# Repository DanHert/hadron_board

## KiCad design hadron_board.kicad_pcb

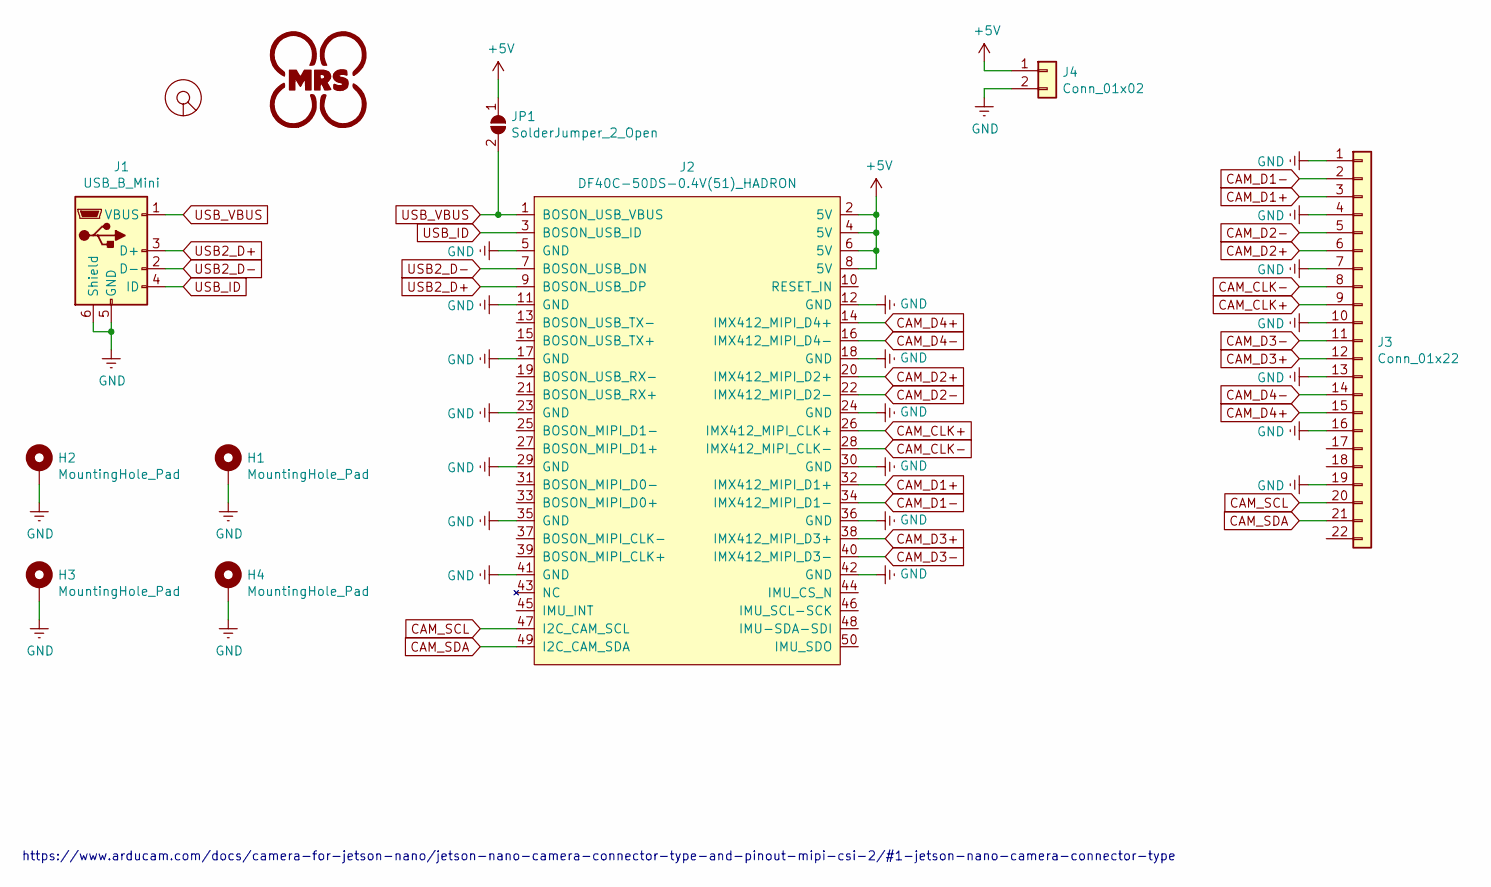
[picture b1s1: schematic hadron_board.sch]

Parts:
G1: LOGO; MRS_10mm
H1, H2, H3, H4: MountingHole_Pad; Mounting_hole_plated_1.7mm
J1: USB_B_Mini; USB_Mini-B_Lumberg_2486_01_Horizontal
J2: DF40C-50DS-0.4V(51)_HADRON; HRS_DF40C-50DS-0.4V(51)
J3: Conn_01x22; MOLEX_54548-2271
J4: Conn_01x02; Header_1x02_P2.54mm
JP1: SolderJumper_2_Open; SolderJumper-2_P1.3mm_Open_TrianglePad1.0x1.5mm
L1: logo; Logo_2mm

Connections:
+5V: J2.2 (5V), J2.4 (5V), J2.6 (5V), J2.8 (5V), J4.1, JP1.1 (A)
CAM_CLK+: J2.26 (IMX412_MIPI_CLK+), J3.9
CAM_CLK-: J2.28 (IMX412_MIPI_CLK-), J3.8
CAM_D1+: J2.32 (IMX412_MIPI_D1+), J3.3
CAM_D1-: J2.34 (IMX412_MIPI_D1-), J3.2
CAM_D2+: J2.20 (IMX412_MIPI_D2+), J3.6
CAM_D2-: J2.22 (IMX412_MIPI_D2-), J3.5
CAM_D3+: J2.38 (IMX412_MIPI_D3+), J3.12
CAM_D3-: J2.40 (IMX412_MIPI_D3-), J3.11
CAM_D4+: J2.14 (IMX412_MIPI_D4+), J3.15
CAM_D4-: J2.16 (IMX412_MIPI_D4-), J3.14
CAM_SCL: J2.47 (I2C_CAM_SCL), J3.20
CAM_SDA: J2.49 (I2C_CAM_SDA), J3.21
GND: H1.1, H2.1, H3.1, H4.1, J1.5 (GND), J1.6 (Shield), J2.5 (GND), J2.11 (GND), J2.12 (GND), J2.17 (GND), J2.18 (GND), J2.23 (GND), J2.24 (GND), J2.29 (GND), J2.30 (GND), J2.35 (GND), J2.36 (GND), J2.41 (GND), J2.42 (GND), J3.1, J3.4, J3.7, J3.10, J3.13, J3.16, J3.19, J3.SH1, J3.SH2, J4.2
USB2_D+: J1.3 (D+), J2.9 (BOSON_USB_DP)
USB2_D-: J1.2 (D-), J2.7 (BOSON_USB_DN)
USB_ID: J1.4 (ID), J2.3 (BOSON_USB_ID)
USB_VBUS: J1.1 (VBUS), J2.1 (BOSON_USB_VBUS), JP1.2 (B)

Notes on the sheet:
https://www.arducam.com/docs/camera-for-jetson-nano/jetson-nano-camera-connector-type-and-pinout-mipi-csi-2/#1-jetson-nano-camera-connector-type

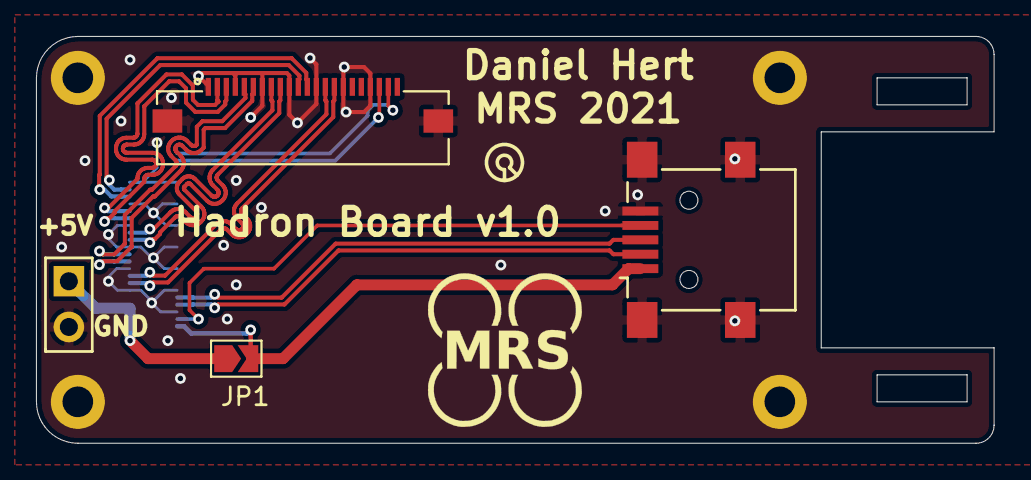
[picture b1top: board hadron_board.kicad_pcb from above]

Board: 2 copper layers, 53.2 x 22.6 mm, 11 parts (1 on the bottom side), 18 nets.

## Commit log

2021-11-05 Added PDFs
